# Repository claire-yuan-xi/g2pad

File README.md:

# G2Pad

G2Pad is a four-key Bluetooth macro pad for the Even Realities G2 smart glasses with fast command input and direct control of the glasses's interface. 

p.s. apologies for the sometimes fuzzy quality of my visuals and posters- I screenshotted them directly from Canva

G2Pad was designed to use four official GitHub keycaps which requires MX-style mechanical switches. The goal of G2Pad is to create a cheaper alternative to the glasses' existing touch and ring controls, as the glasses alone cost upwards of 600 bucks with prescriptions and an extra $300 for the gadget 'R1 ring.' Using a macro pad for control allows for better physical feedback as well. 

The main personal reason I built G2Pad was also to show my dad the product of his monetary investment in me in the form of a dedicated electronics build for him and also to repay him for paying for these expensive smart glasses. 

Also special thanks to my teachers and friends involved in helping me develop these visuals and posters!!

## How to use G2Pad
1. slide the left switch to ON
2. on your phone, open bluetooth and pair with 'G2Pad' 
3. open an Even Hub app on your phone that listens for G2Pads keys (this is the part im building next after funding and hardware)
4. use the four keys to move around the glasses (controls listed below under 'controls')
5. to charge, plug a usb-c cable into the XIAO with the power switch to ON
## Features
+ 4 MX-style mechanical switches
+ Seeed Studio XIAO nRF52840 with Bluetooth Low Energy
+ 150 mAh LiPo battery- charges with USB-C
+ On/Off slide switch
+ Auto Sleep functionality
+ Custom 42 x 64 mm PCB
+ 3D printed 47 x 69 x 16 mm case with a lanyard hole
+ Open source ZMK firmware

## Controls

Each key has a dedicated message that directs to the phone in the form of a letter. The keys 'back' and 'select' specifically do a second function if held down for longer than 0.4 seconds. Each keys control is as follows:

There are also two combos:
+ pressing 'up' and 'down' together turns Nav mode on or off, which changes the keys to arrows enter and esc
+ holding 'back' and 'select' together opens the Bluetooth function, which makes 'up' the button to switch to the next paired device and then 'down' to forget the current pairing

### How G2Pad works
G2Pad doesn't take keyboard input on its own, so I made the glasses-connected phone sort of like a middleman which connects to both the glasses and G2Pad via standard Bluetooth HID. The Even Realities app will capture these keystrokes and send corresponding commands to teh glasses over bluetooth. 
The Even Hub app hasn't been built yet, but after I receive funding that will be my next step!
## Case
The case was modeled in FreeCAD and was designed to be printed in 2 parts:
+ the bottom tray, which holds the battery under the PCB and has three standoffs, the USB-C opening, the slot for the power switch, and the lanyard hole
+ the top plate, which is a 1.5 mm switch plate with screw bosses, a pocket for the XIAO underneath, and a recess for a name badge

The parts are held together with three M2 x 12 mm screws that go up thru the tray and the PCB into the top plate. 
## PCB
Using KiCAD, the PCB ended up being 2 layers with a ground pour on both sides. The XIAO will be soldered onto the board at the bottom, and I'll put the four switches above the XIAO. The power switch is on the left edge of the first image attached here, and the battery plugs into a JST connector on the back of the board.

two short wires connect the board to the BAT+ and BAT- pads on the underside of the XIAO. 

the gerbers are in pcb/gerbers.zip and can be ordered from JLCPCB.
## Schematic

## Firmware
G2Pad's firmware runs on ZMK, which is open source firmware for wireless keyboards. I didn't compile the firmware on my own mac either so instead I made a Github actions workflow. To change what the keys do, edit firmware/g2pad.keymap.

## Bill of Materials
The parts come out to about $168 without tools and $263.10 with tools and shipping. See [BOM.csv](BOM.csv) for the full list of parts

## Build Steps

1. get all materials from the bom and order them (including the pcb from JLCPCB) then 3d print the bottom and top trays
2. clean up the prints
3. soldering!! i will finish this section once i actually get my hardware but from my understanding ill def have to solder the BAT pads on the XIAO then solder the XIAO to the board
4. put the MX switches into the top plate then line the pins up with the pcb then solder them in
5. flash the firmware 
6. set the LiPo into the tray and plug into the JST socket
7. screwing!! line up the pcb and plate and screw everything tg
8. press on the four keycaps
9. Done! pair 'g2pad' over bluetooth to the phone and start clicking thru ur g2.

## Credits

Inspired by Ben Vallack, a developer on YouTube who created his own macro pad for his Even Realities G2 glasses. None of his code is open-sourced and most of his tutorials and methodology are locked behind paywalls anyways. No tutorials were followed.

The XIAO nRF52840 and the glasses in my posters are placeholders. Keycaps by [Github](https://thegithubshop.com/products/1542509-00-key-caps-assorted-pack-of-8), firmware by [ZMK](https://zmk.dev/).

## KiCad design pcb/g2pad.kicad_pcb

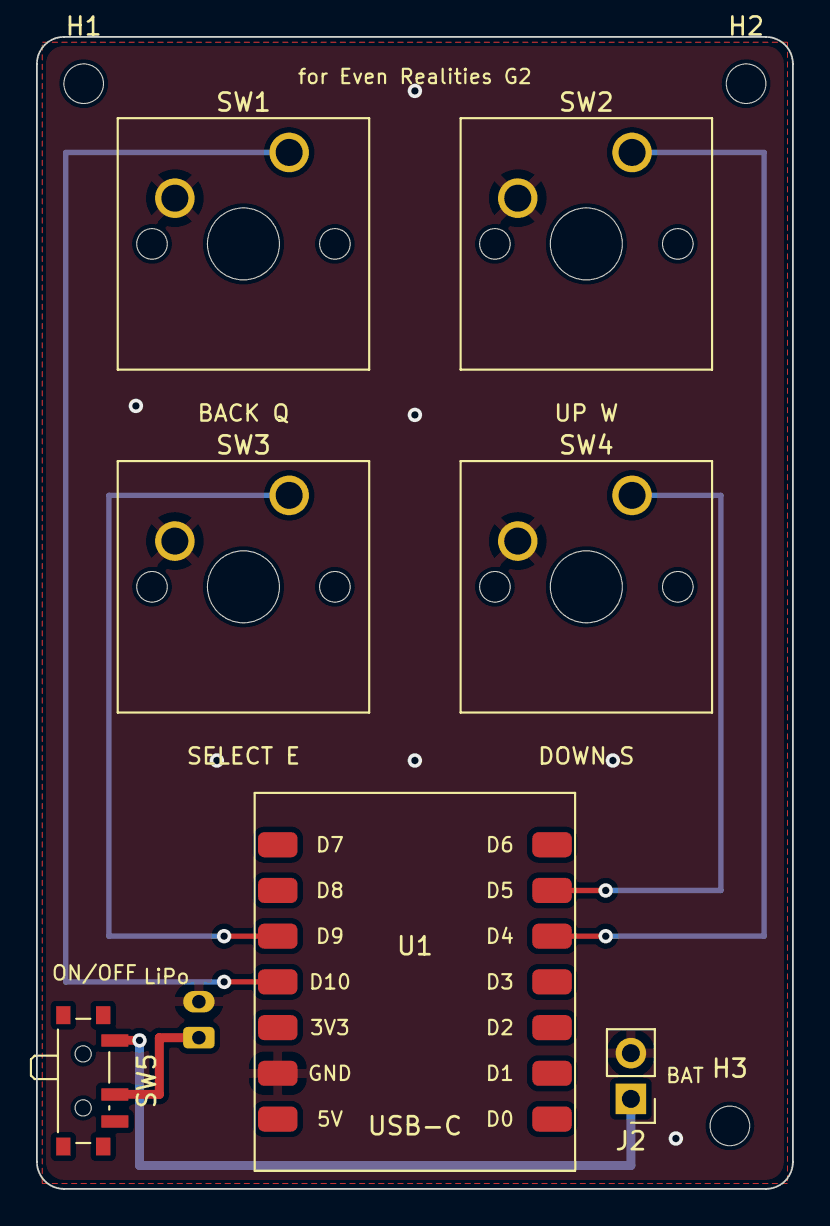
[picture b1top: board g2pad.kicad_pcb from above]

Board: 2 copper layers, 42.0 x 64.0 mm, 11 parts (1 on the bottom side), 7 nets.

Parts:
H1, H2, H3: M2; MountingHole_2.2mm_M2
J1: LiPo (JST-PH); JST_PH_B2B-PH-K_1x02_P2.00mm_Vertical
J2: BAT wires; PinHeader_1x02_P2.54mm_Vertical
SW1, SW2, SW3, SW4: MX_Switch; SW_Cherry_MX_1.00u_PCB
SW5: Power (PCM12); SW_SPDT_PCM12
U1: XIAO_nRF52840; XIAO_nRF52840_SMD

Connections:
BAT_RAW: J1.1, SW5.2
GND: J1.2, J2.2, SW1.2, SW2.2, SW3.2, SW4.2, U1.13 (GND)
K_BACK: SW1.1, U1.11 (D10)
K_DOWN: SW4.1, U1.6 (D5)
K_SELECT: SW3.1, U1.10 (D9)
K_UP: SW2.1, U1.5 (D4)
VBAT: J2.1, SW5.1

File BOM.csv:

Item,Ref,Qty,Unit price (USD),Total (USD),Owned?,Link,Notes
Macro Pad keycaps (MX stem),Keycaps,1,17.00,17.00,No,https://thegithubshop.com/products/1542509-00-key-caps-assor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,Official GitHub keycaps from the GitHub Shop; MX cross stem
Seeed Studio XIAO nRF52840,U1,1,14.90,14.90,No,https://www.seeedstudio.com/Seeed-XIAO-BLE-nRF52840-p-5201.html,"BLE 5 MCU, USB-C, built-in LiPo charger; runs ZMK"
MX-style mechanical switches (5-pin),SW1-SW4,4,0.40,9.00,No,https://www.amazon.com/s?k=gateron+mx+switches+5+pin,Any 5-pin MX switch; PCB-mount pegs match the footprint
LiPo battery 3.7 V 150 mAh with JST-PH,BT1,1,8.95,8.95,No,https://www.adafruit.com/products/1317,19.75 x 26 x 3.8 mm; fits the pocket under the PCB
JST-PH 2-pin vertical socket (B2B-PH-K-S),J1,1,5.20,5.20,No,https://www.digikey.com/en/products/detail/jst-sales-america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,Mounted on the back of the PCB
C&K PCM12SMTR side slide switch,SW5,1,5.65,5.65,No,https://www.digikey.com/en/products/detail/c-k/PCM12SMTR/1640112,"Power on/off, lever pokes out of the left wall"
G2Pad PCB (2-layer 42 x 64 mm 1.6 mm),PCB,5,0.40,7.00,No,https://jlcpcb.com/,Upload pcb/gerbers.zip; plus shipping
3D-printed bottom tray + top plate (PLA/PETG),Enclosure,1,10.00,10.00,No,https://jlcpcb.com/3d-printing,cad/step/g2pad_bottom_tray.step and g2pad_top_plate.step
M2 x 12 mm screws (self-tapping),H1-H3,3,0.10,5.30,No,https://www.amazon.com/s?k=m2+self+tapping+screws+kit,Screw up through the tray and PCB into the plate bosses
30 AWG silicone wire,J2 to XIAO,10,0.10,5.10,No,https://www.amazon.com/s?k=30+awg+silicone+wire,Two short leads from J2 to the XIAO BAT+ / BAT- pads
Temperature-controlled soldering iron kit,Tool,1,25.00,25.00,No,https://www.amazon.com/s?k=temperature+controlled+soldering+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,"Adjustable temp with stand, sponge/brass cleaner and spare tips"
Rosin-core solder 0.8 mm (63/37),Tool,1,13.00,13.00,No,https://www.amazon.com/s?k=63%2F37+rosin+core+solder+0.8mm,Thin solder for the switch pins and XIAO pads
No-clean flux pen,Tool,1,12.00,12.00,No,https://www.amazon.com/s?k=no+clean+flux+pen,Makes the small XIAO and slide switch joints much easier
Solder wick (desoldering braid),Tool,1,10.00,10.00,No,https://www.amazon.com/s?k=solder+wick+desoldering+braid,For fixing bridges and mistakes
Flush cutters,Tool,1,12.00,12.00,No,https://www.amazon.com/s?k=flush+cutters+electronics,Trim leads and wire
Wire strippers (20-30 AWG),Tool,1,15.00,15.00,No,https://www.amazon.com/s?k=wire+stripper+30+awg,Must go down to 30 AWG for the battery leads
ESD-safe precision tweezers,Tool,1,11.00,11.00,No,https://www.amazon.com/s?k=esd+precision+tweezers+set,Holds the slide switch and JST socket while soldering
Digital multimeter,Tool,1,20.00,20.00,No,https://www.amazon.com/s?k=digital+multimeter+continuity,Measures electrical properties like voltage
Helping hands / PCB holder,Tool,1,17.00,17.00,No,https://www.amazon.com/s?k=pcb+holder+helping+hands+soldering,Holds the board steady while soldering
Precision screwdriver set,Tool,1,15.00,15.00,No,https://www.amazon.com/s?k=precision+screwdriver+set,Phillips bits for the M2 case screws
USB-C data cable,Tool,1,13.00,13.00,No,https://www.amazon.com/s?k=usb+c+data+cable,Must support data (not charge-only) to flash the ZMK firmware
Kapton tape,Tool,1,12.00,12.00,No,https://www.amazon.com/s?k=kapton+tape,Insulates the battery and XIAO underside
